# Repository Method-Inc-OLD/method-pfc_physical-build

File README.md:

# Method Personal Food Computer – Physical Build

Documentation of the mechanical and electrical design of [Method](Http://www.method.com)'s Personal Food Computer 

## Overview
The Method PFC is a version of OpenAg's Personal Food Computer. It was built to be more modular and incorporate recycled material. This repository contains:
- [Mechanical](/Mechanical) (Construction and 3D prints)
- [Electrical](/Electrical) (Circuitry)

For Method's custom software, please visit the [method-pfc_device-software](http://www.github.com/method-inc/method-pfc_device-software) repository.

## Credits

Method PFC v1.0 was designed and built by David Mayman, Felix Noller, Adrian Kraus, and Luke Thompson in London.

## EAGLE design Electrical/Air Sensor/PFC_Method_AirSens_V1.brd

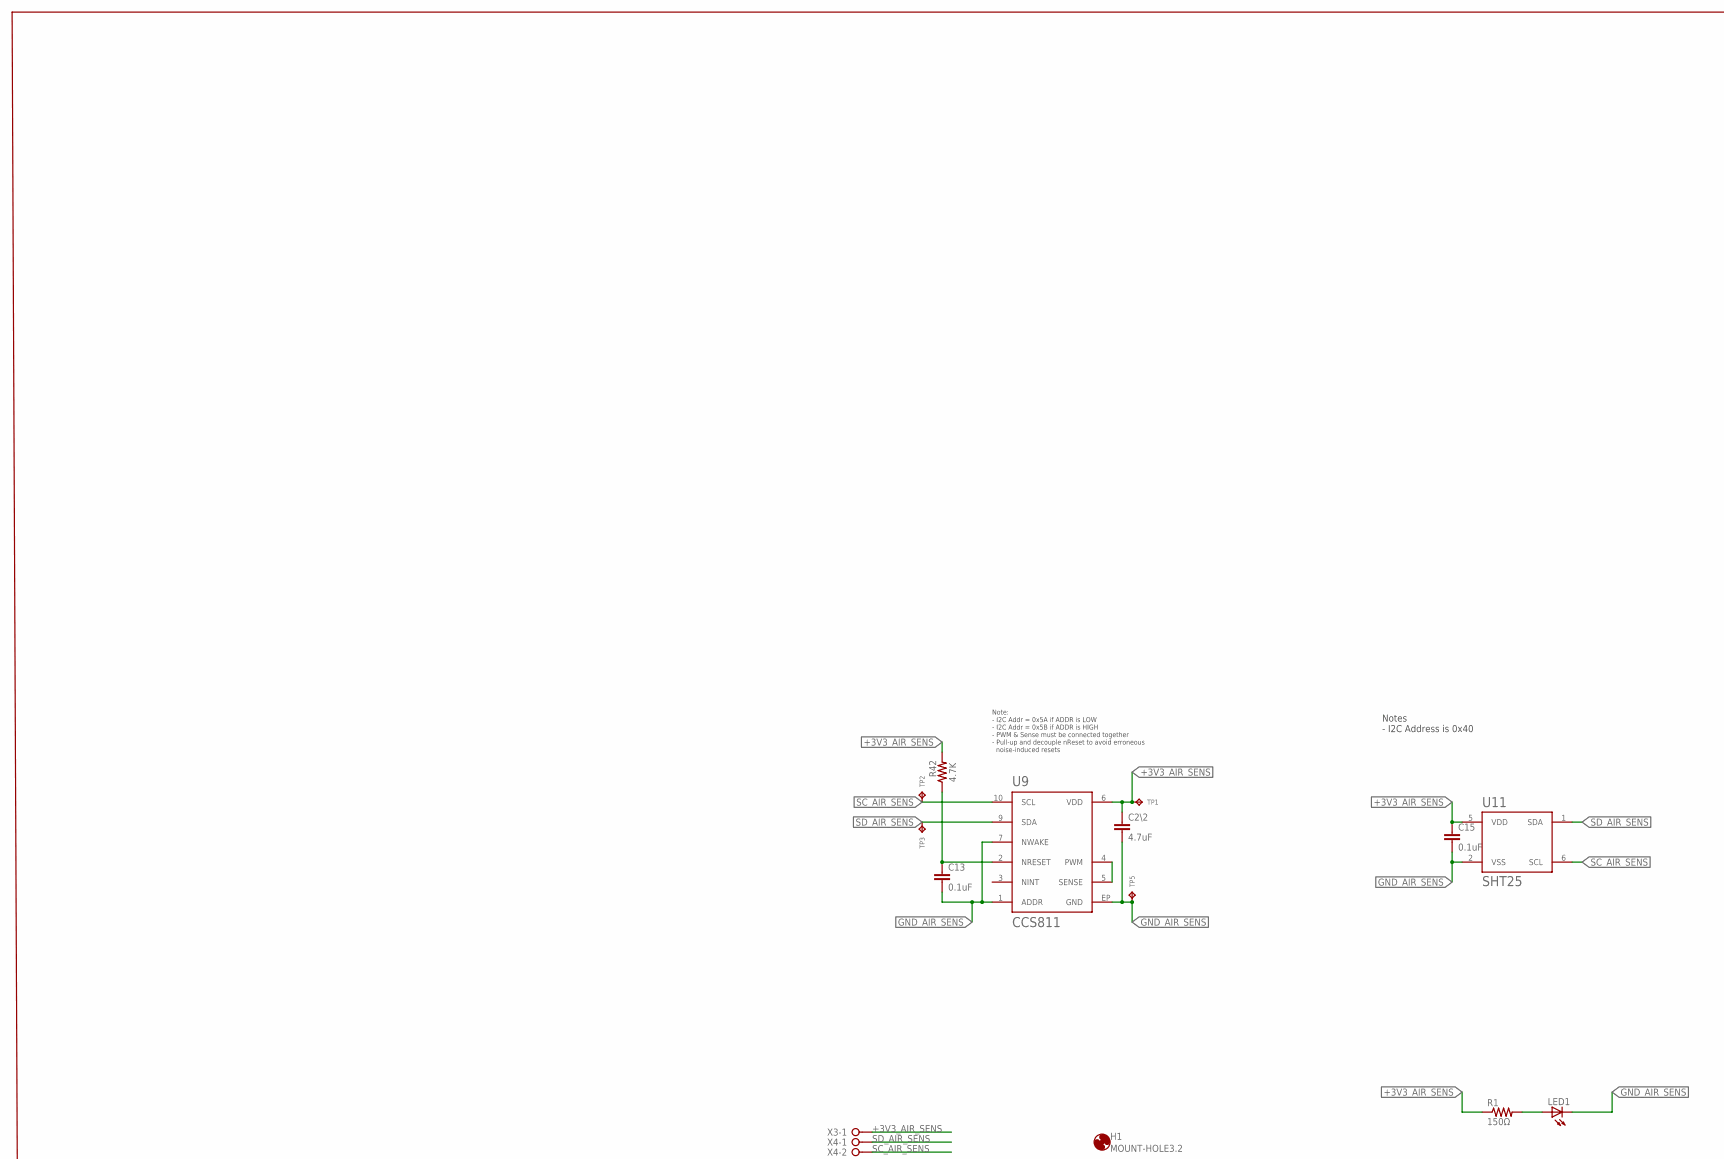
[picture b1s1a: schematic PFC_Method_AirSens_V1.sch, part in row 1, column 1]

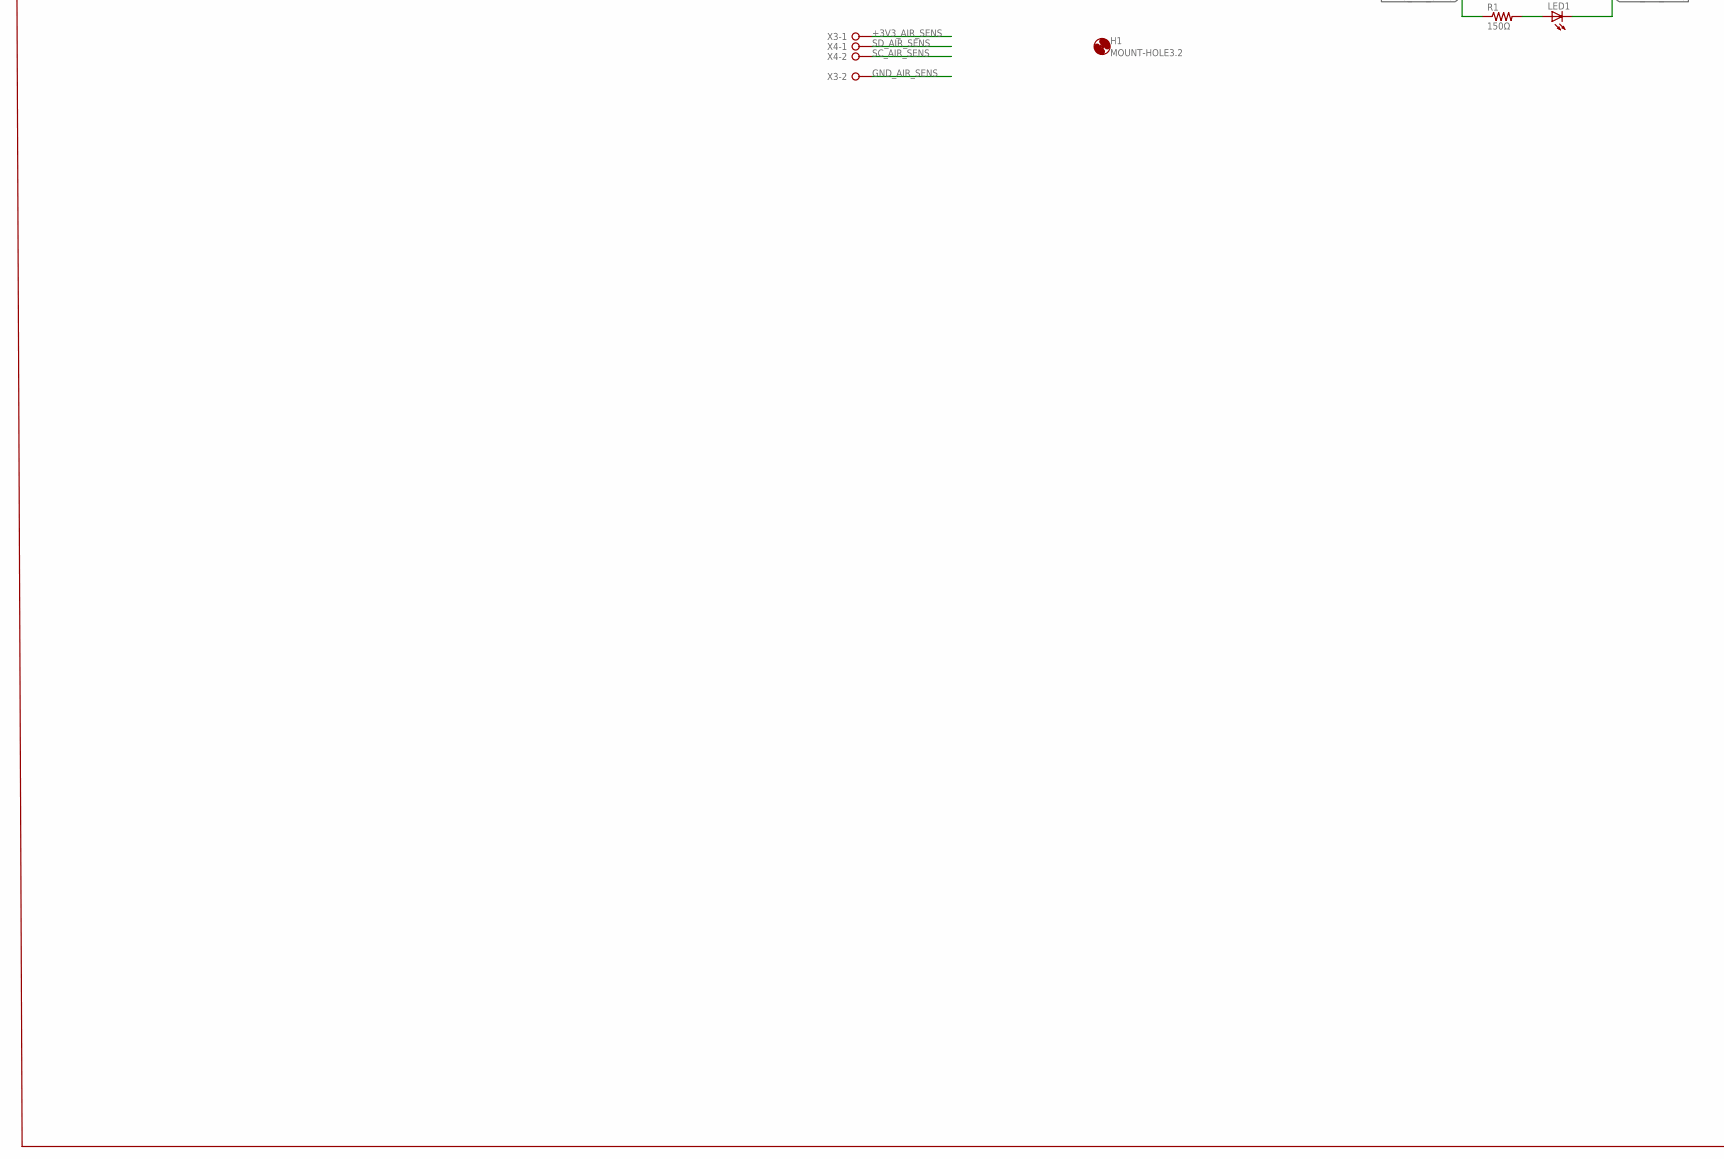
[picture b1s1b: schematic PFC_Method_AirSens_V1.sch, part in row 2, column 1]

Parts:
C2\2: 4.7uF; C0805
C13, C15: 0.1uF; C0603
H1: MOUNT-HOLE3.2; 3,2
LED1: LED5MM
R1: 150Ω; 0207/10
R42: 4.7K; R1206
TP1, TP2, TP3, TP5: TPTP06R; TP06R
U9: CCS811
U11: SHT25; SHT2X
X3, X4: W237-02P; W237-132

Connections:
+3V3_AIR_SENS: C2\2.1, C15.1, R1.1, R42.2, TP1.TP, U9.6 (VDD), U11.5 (VDD), X3.1
GND_AIR_SENS: C2\2.2, C13.2, C15.2, LED1.K (C), TP5.TP, U9.1 (ADDR), U9.7 (NWAKE), U9.EP (GND), U11.2 (VSS), X3.2
unnamed: LED1.A, R1.2
unnamed: U9.4 (PWM), U9.5 (SENSE)
unnamed: C13.1, R42.1, U9.2 (NRESET)
SC_AIR_SENS: TP2.TP, U9.10 (SCL), U11.6 (SCL), X4.2
SD_AIR_SENS: TP3.TP, U9.9 (SDA), U11.1 (SDA), X4.1

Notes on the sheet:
Original Board by Dan Poitrast
Change Log:
Released under the Creative Commons Attribution Share-Alike 4.0 License https://creativecommons.org/licenses/by-sa/4.0/
Note: - I2C Addr = 0x5A if ADDR is LOW - I2C Addr = 0x5B if ADDR is HIGH - PWM & Sense must be connected together - Pull-up and decouple nReset to avoid erroneous noise-induced resets
Notes - I2C Address is 0x40

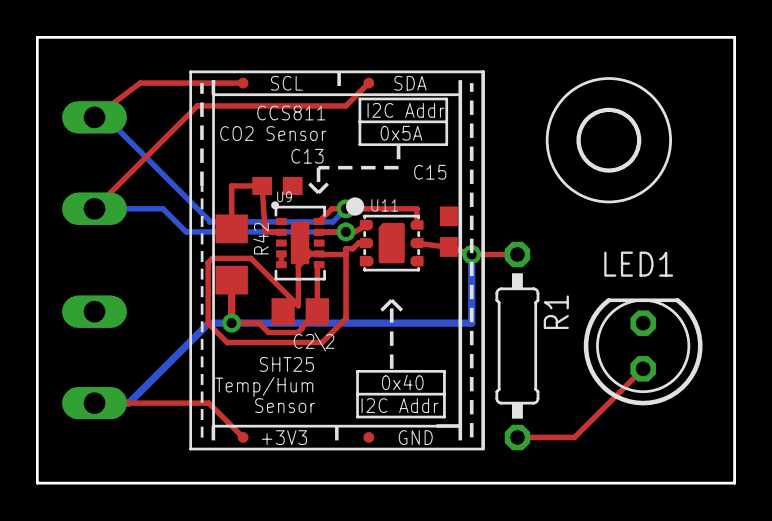
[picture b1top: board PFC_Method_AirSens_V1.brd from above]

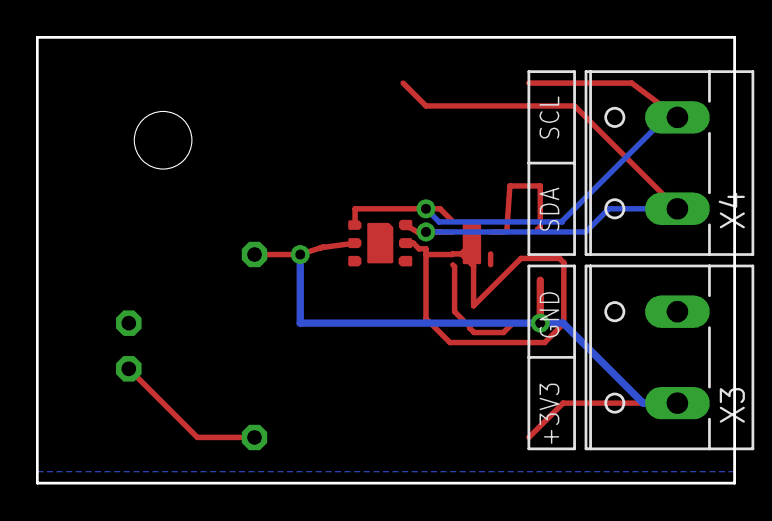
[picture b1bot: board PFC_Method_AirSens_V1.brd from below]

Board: 2 copper layers, 38.7 x 24.8 mm, 15 parts (2 on the bottom side), 7 nets.

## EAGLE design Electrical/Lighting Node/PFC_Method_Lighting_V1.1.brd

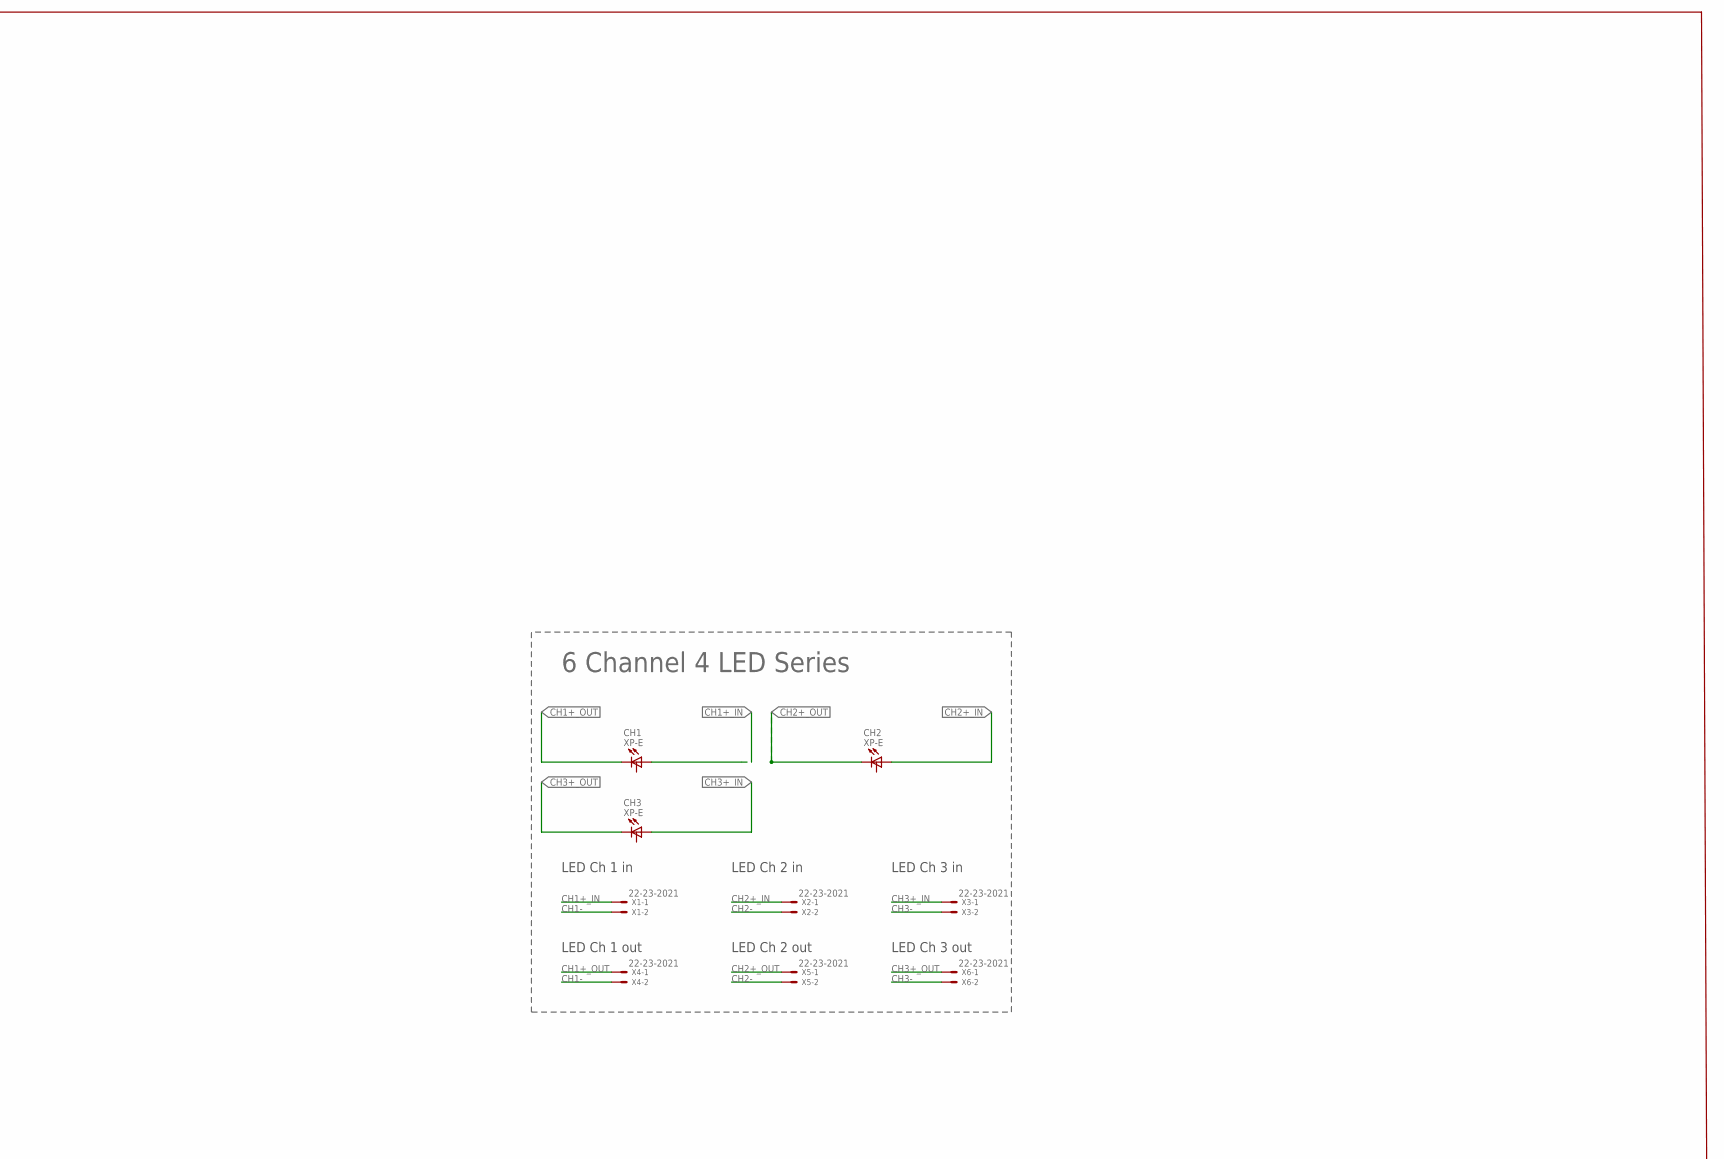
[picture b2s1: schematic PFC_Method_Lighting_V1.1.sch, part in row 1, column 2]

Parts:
CH1, CH2, CH3: XP-E; CREE-XLAMP-XP-E
X1, X2, X3, X4, X5, X6: 22-23-2021

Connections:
CH1+_IN: CH1.A, CH1.A@1 (A), X1.1
CH1+_OUT: CH1.C, CH1.C@1 (C), X4.1
CH1-: X1.2, X4.2
CH2+_IN: CH2.A, CH2.A@1 (A), X2.1
CH2+_OUT: CH2.C, CH2.C@1 (C), X5.1
CH2-: X2.2, X5.2
CH3+_IN: CH3.A, CH3.A@1 (A), X3.1
CH3+_OUT: CH3.C, CH3.C@1 (C), X6.1
CH3-: X3.2, X6.2

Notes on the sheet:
Original Board by Dan Poitrast
Change Log:
Released under the Creative Commons Attribution Share-Alike 4.0 License https://creativecommons.org/licenses/by-sa/4.0/
6 Channel 4 LED Series
LED Ch 1 out
LED Ch 2 out
LED Ch 3 out
LED Ch 1 in
LED Ch 2 in
LED Ch 3 in

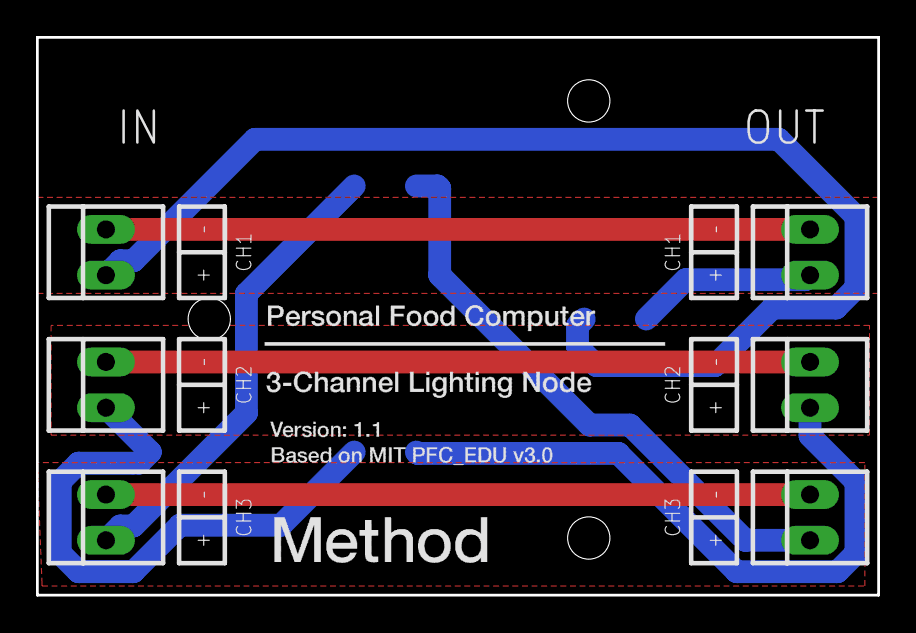
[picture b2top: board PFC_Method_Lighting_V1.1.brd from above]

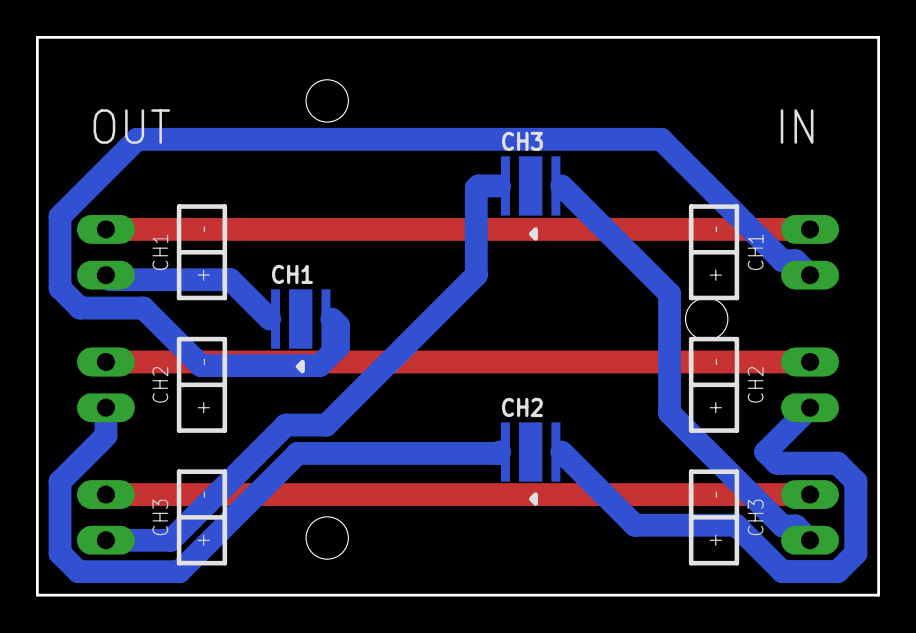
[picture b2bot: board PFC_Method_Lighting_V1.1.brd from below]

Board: 2 copper layers, 46.7 x 31.0 mm, 9 parts (3 on the bottom side), 9 nets.

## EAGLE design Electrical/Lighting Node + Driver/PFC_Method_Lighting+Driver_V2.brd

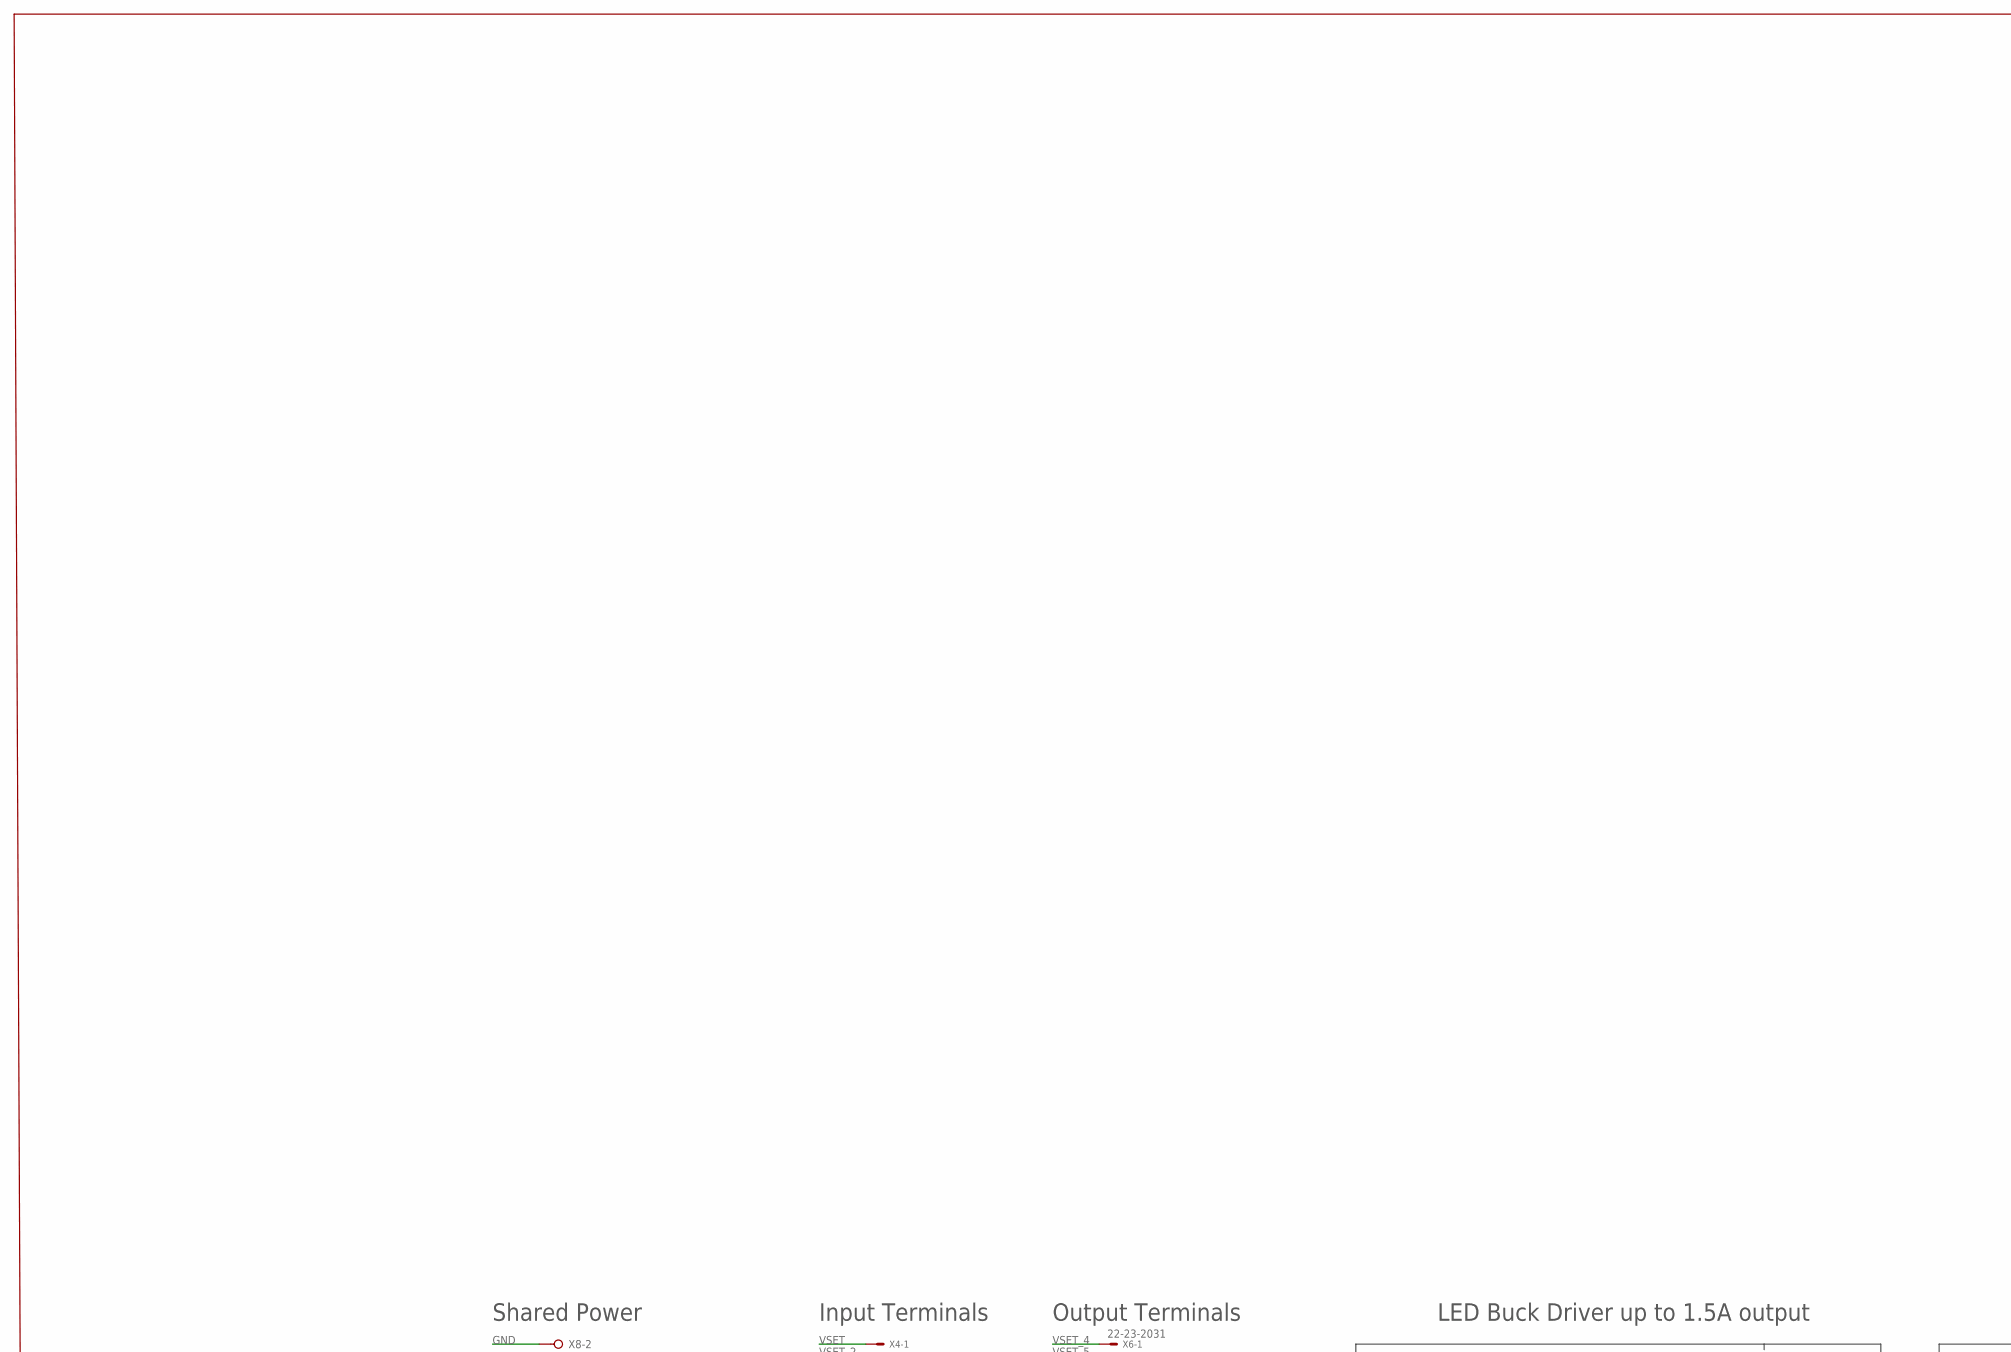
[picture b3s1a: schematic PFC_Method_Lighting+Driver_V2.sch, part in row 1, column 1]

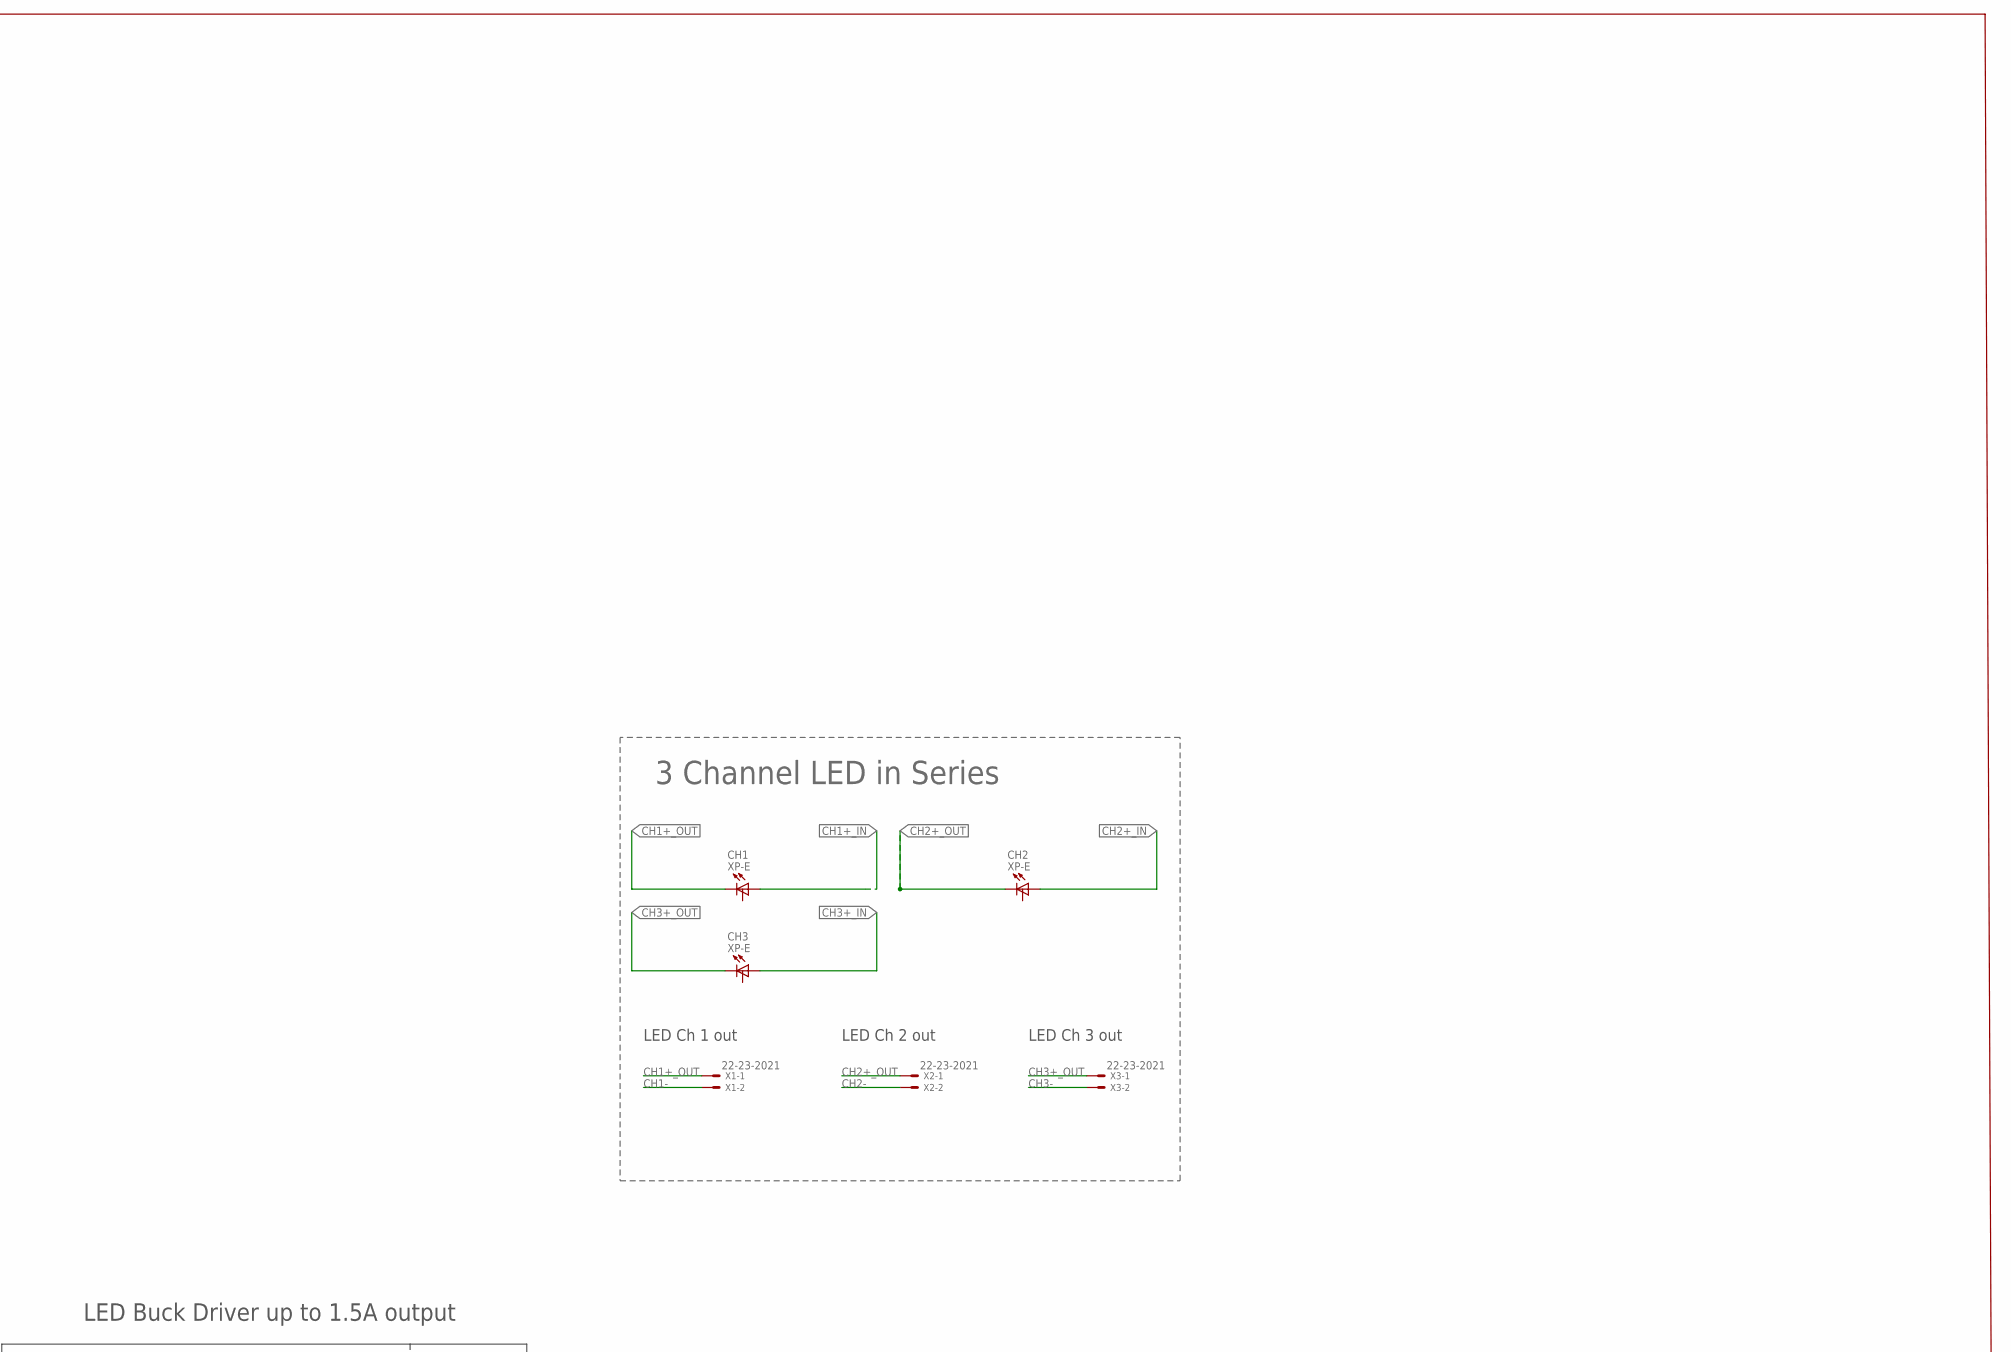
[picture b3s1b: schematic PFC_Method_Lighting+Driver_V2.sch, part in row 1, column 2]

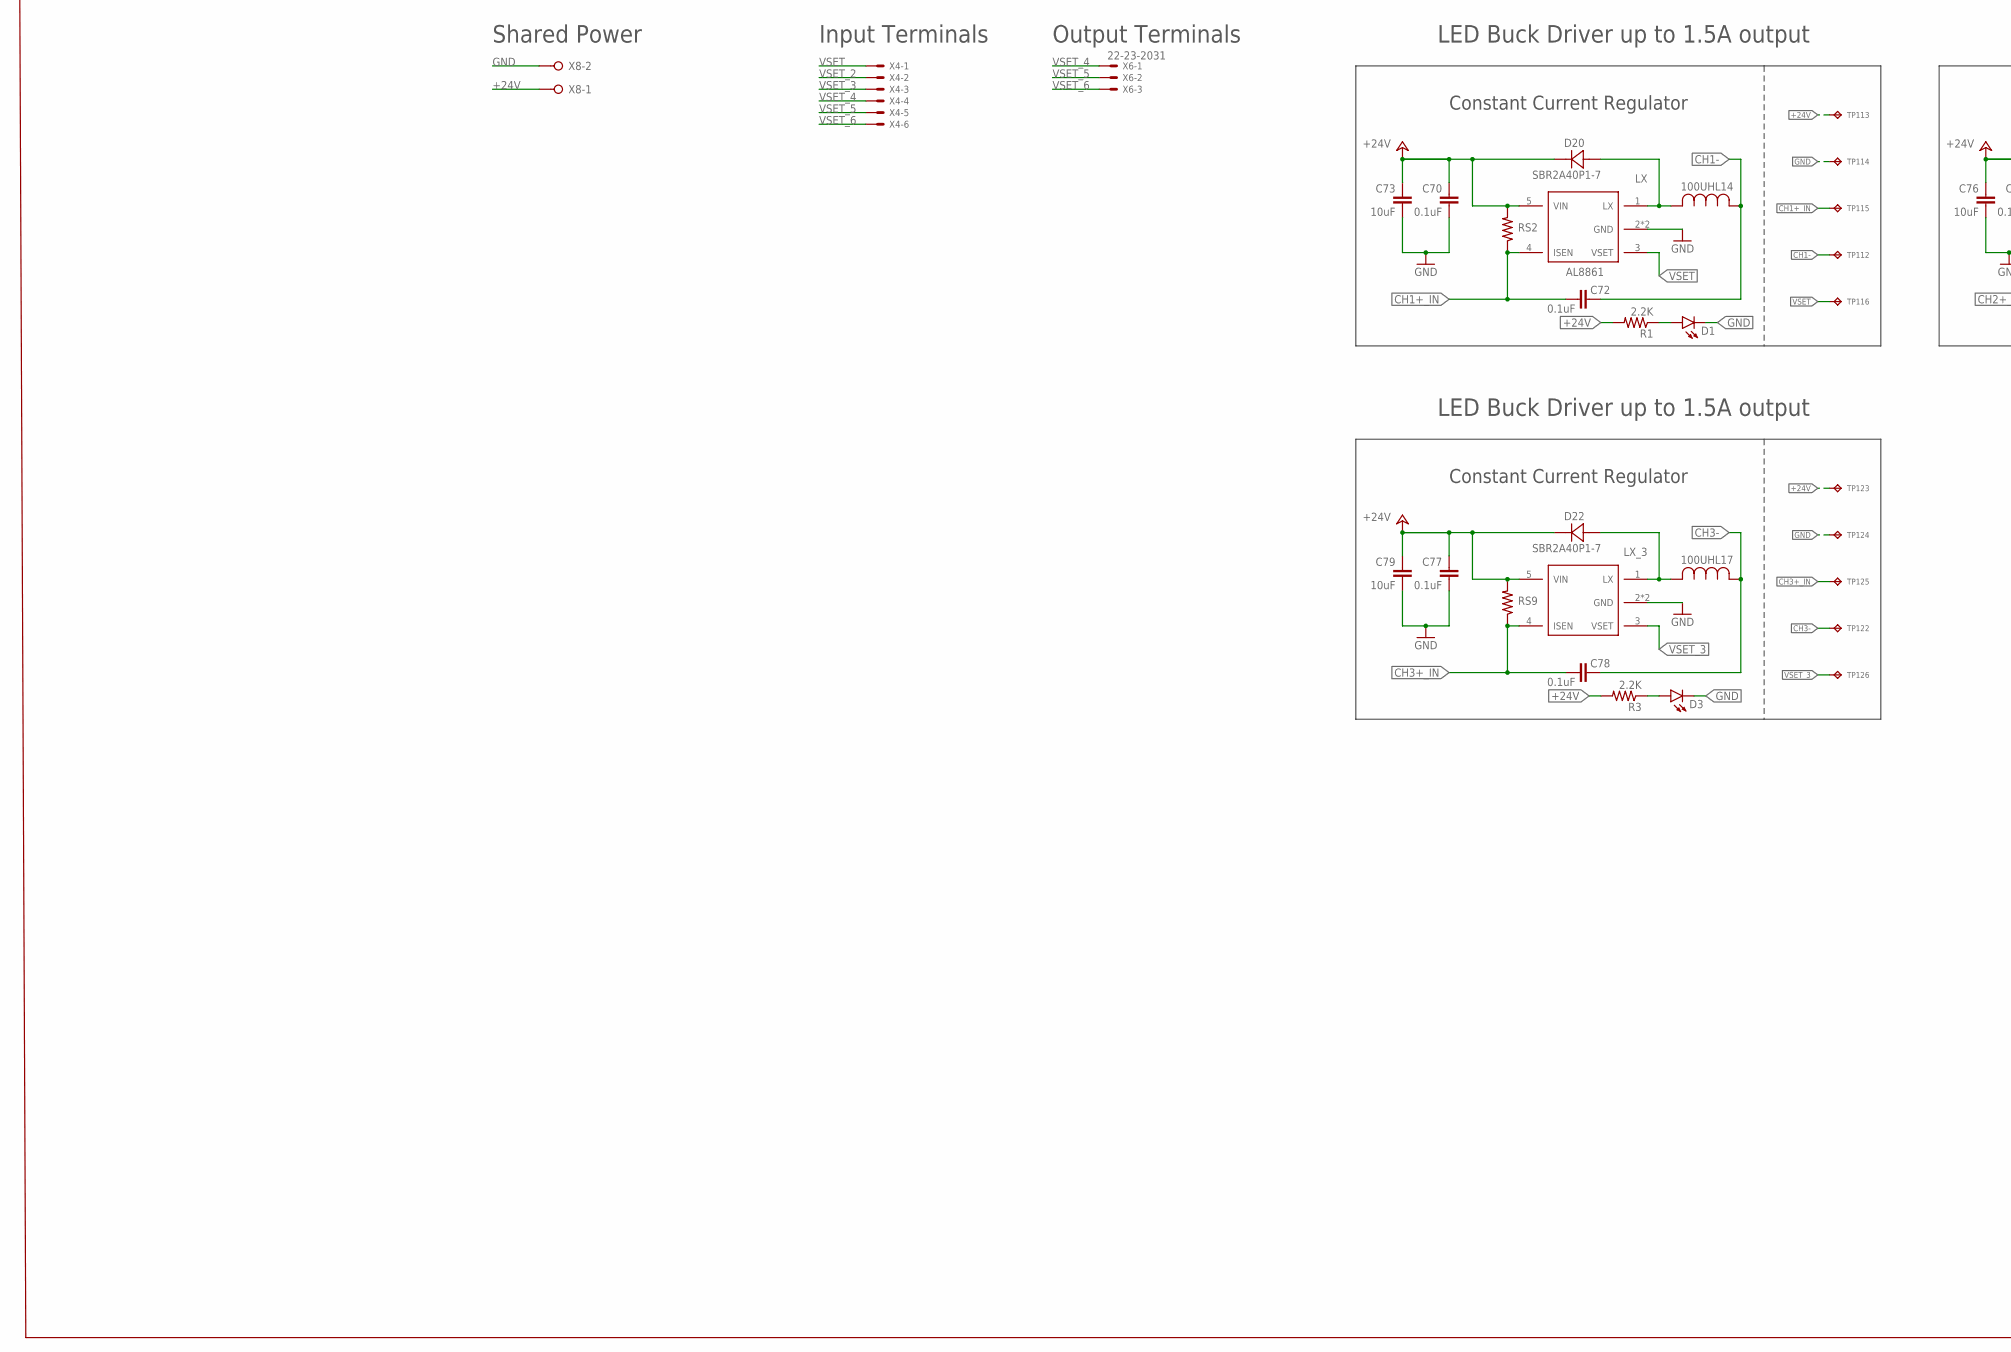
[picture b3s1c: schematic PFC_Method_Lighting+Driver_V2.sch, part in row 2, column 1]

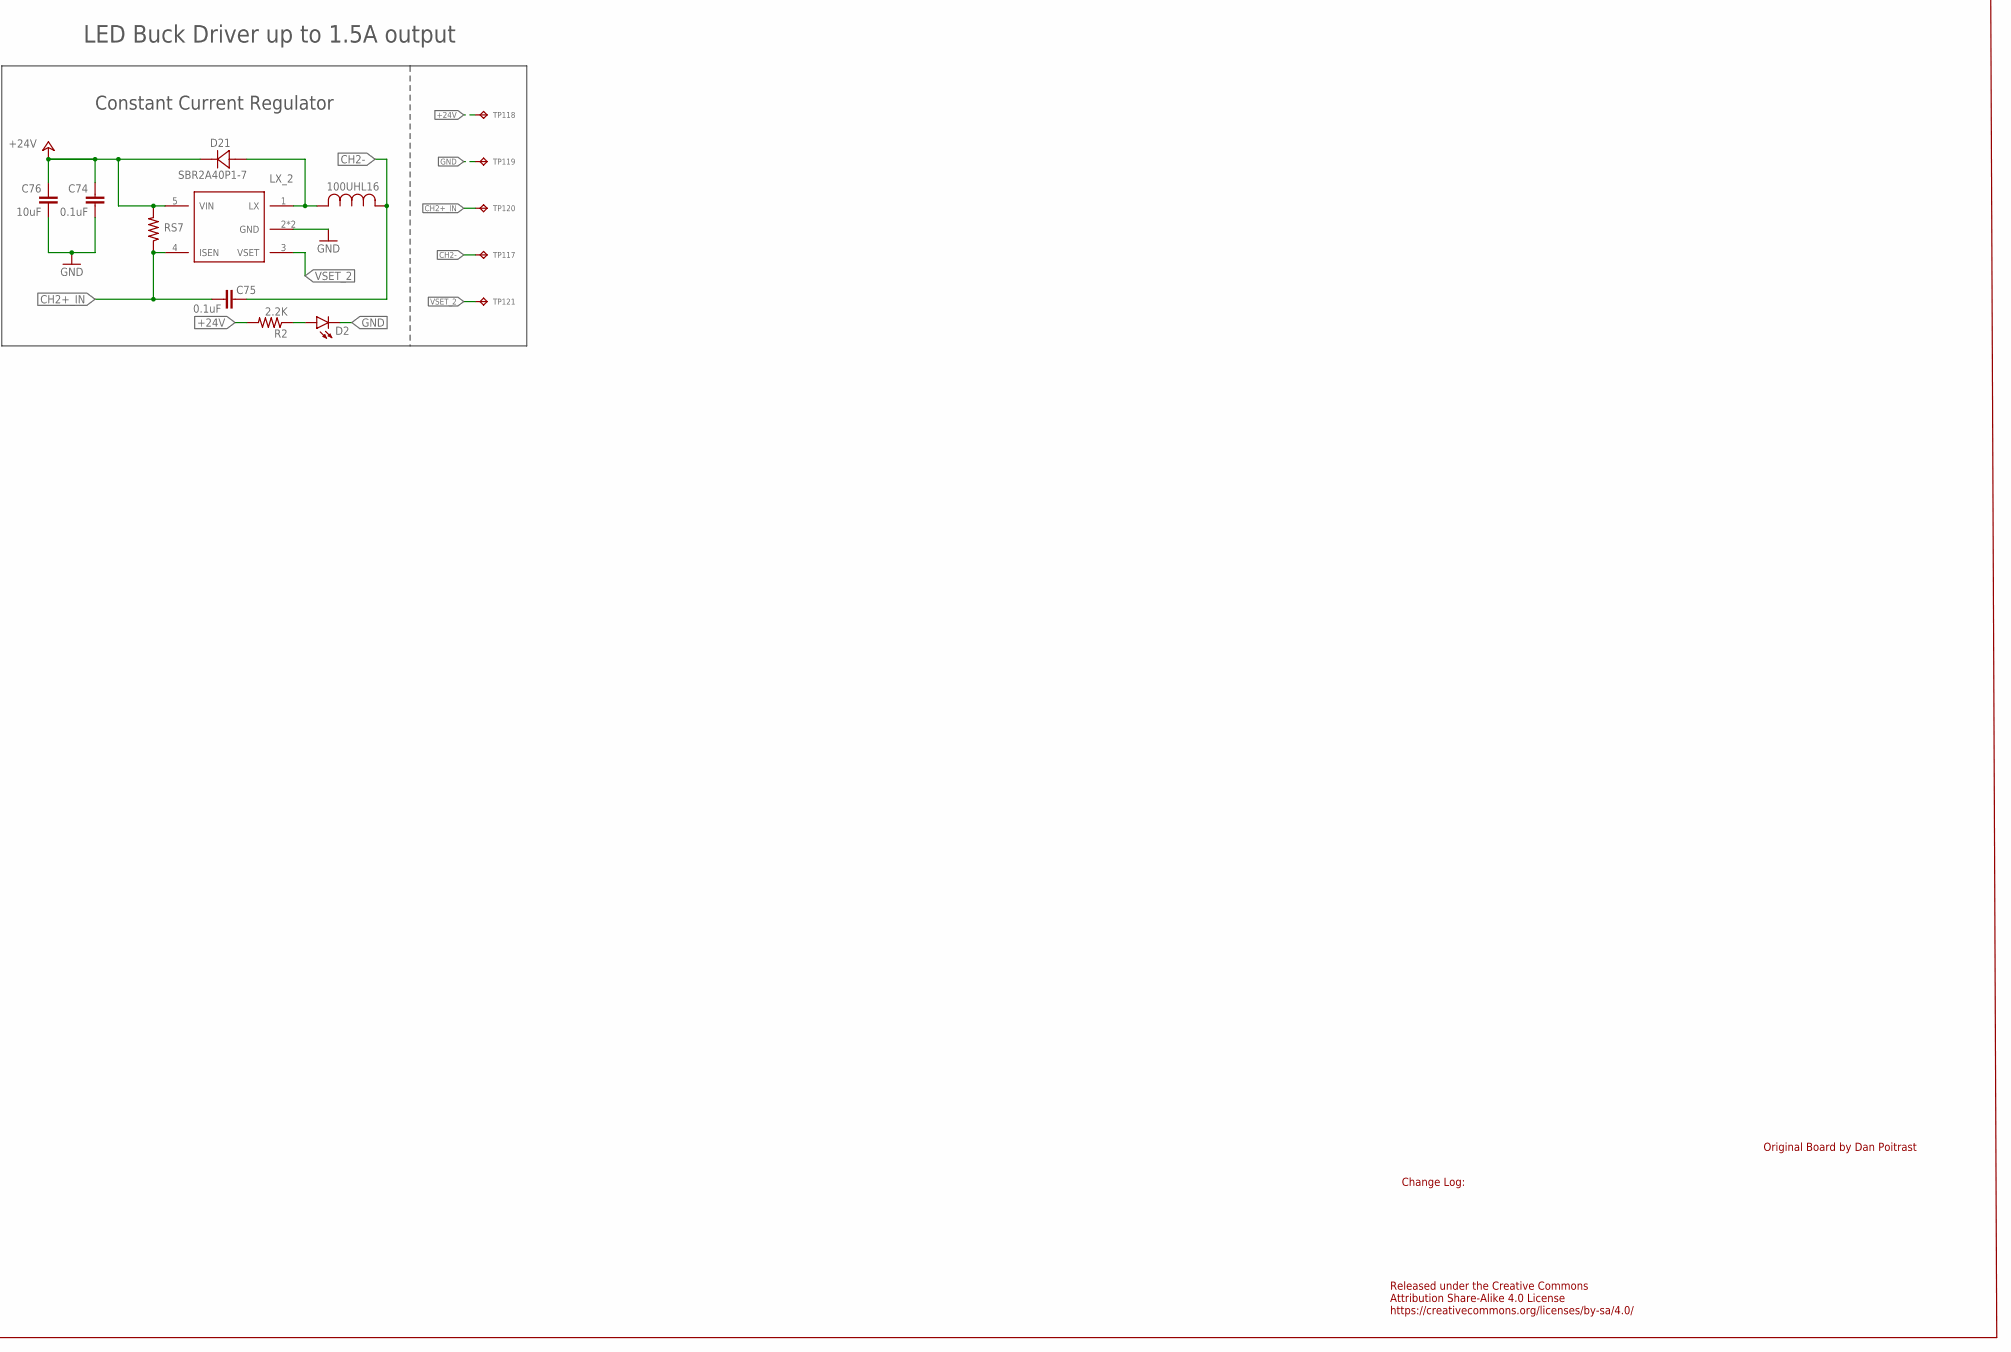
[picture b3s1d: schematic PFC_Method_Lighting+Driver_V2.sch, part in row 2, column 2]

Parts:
C70, C72, C74, C75, C77, C78: 0.1uF; C0603
C73, C76, C79: 10uF; C0805
CH1, CH2, CH3: XP-E; CREE-XLAMP-XP-E
D1, D2, D3: LED5MM; LED_5MM
D20, D21, D22: SBR2A40P1-7; POWERDI123
L14, L16, L17: 100UH; IND_BOURNS_SDR1307
R1, R2, R3: 2.2K; 0207/10
RS2: 6.34Ω; R0805
RS7, RS9: 6.34 Ω; R0805
TP112, TP113, TP114, TP115, TP116, TP117, TP118, TP119, TP120, TP121, TP122, TP123, TP124, TP125, TP126: TPTP06R; TP06R
U$25, U$26, U$27: AL8861
X1, X2, X3: 22-23-2021
X4: 22-23-2061
X6: 22-23-2031
X8: W237-02P; W237-132

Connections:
+24V: C70.1, C73.1, C74.1, C76.1, C77.1, C79.1, D20.-, D21.-, D22.-, R1.2, R2.2, R3.2, RS2.2, RS7.2, RS9.2, TP113.TP, TP118.TP, TP123.TP, U$25.5 (VIN), U$26.5 (VIN), U$27.5 (VIN), X8.1
CH1+_IN: C72.2, CH1.A, CH1.A@1 (A), RS2.1, TP115.TP, U$25.4 (ISEN)
CH1+_OUT: CH1.C, CH1.C@1 (C), X1.1
CH1-: C72.1, L14.2, TP112.TP, X1.2
CH2+_IN: C75.2, CH2.A, CH2.A@1 (A), RS7.1, TP120.TP, U$26.4 (ISEN)
CH2+_OUT: CH2.C, CH2.C@1 (C), X2.1
CH2-: C75.1, L16.2, TP117.TP, X2.2
CH3+_IN: C78.2, CH3.A, CH3.A@1 (A), RS9.1, TP125.TP, U$27.4 (ISEN)
CH3+_OUT: CH3.C, CH3.C@1 (C), X3.1
CH3-: C78.1, L17.2, TP122.TP, X3.2
GND: C70.2, C73.2, C74.2, C76.2, C77.2, C79.2, D1.K (C), D2.K (C), D3.K (C), TP114.TP, TP119.TP, TP124.TP, U$25.2 (GND), U$25.44 (GND), U$26.2 (GND), U$26.44 (GND), U$27.2 (GND), U$27.44 (GND), X8.2
LX: D20.+, L14.1, U$25.1 (LX)
LX_2: D21.+, L16.1, U$26.1 (LX)
LX_3: D22.+, L17.1, U$27.1 (LX)
unnamed: D2.A, R2.1
unnamed: D1.A, R1.1
unnamed: D3.A, R3.1
VSET: TP116.TP, U$25.3 (VSET), X4.1
VSET_2: TP121.TP, U$26.3 (VSET), X4.2
VSET_3: TP126.TP, U$27.3 (VSET), X4.3
VSET_4: X4.4, X6.1
VSET_5: X4.5, X6.2
VSET_6: X4.6, X6.3

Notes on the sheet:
Original Board by Dan Poitrast
Change Log:
Released under the Creative Commons Attribution Share-Alike 4.0 License https://creativecommons.org/licenses/by-sa/4.0/
3 Channel LED in Series
LED Buck Driver up to 1.5A output
Constant Current Regulator
LED Ch 1 out
LED Ch 2 out
LED Ch 3 out
Input Terminals
Output Terminals
Shared Power
AL8861

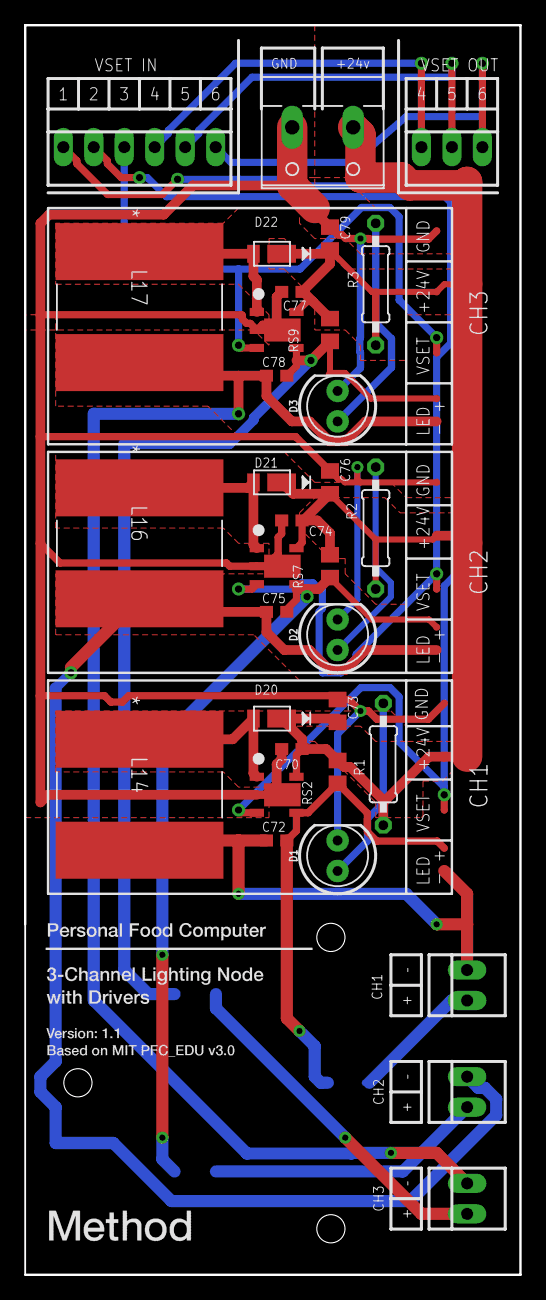
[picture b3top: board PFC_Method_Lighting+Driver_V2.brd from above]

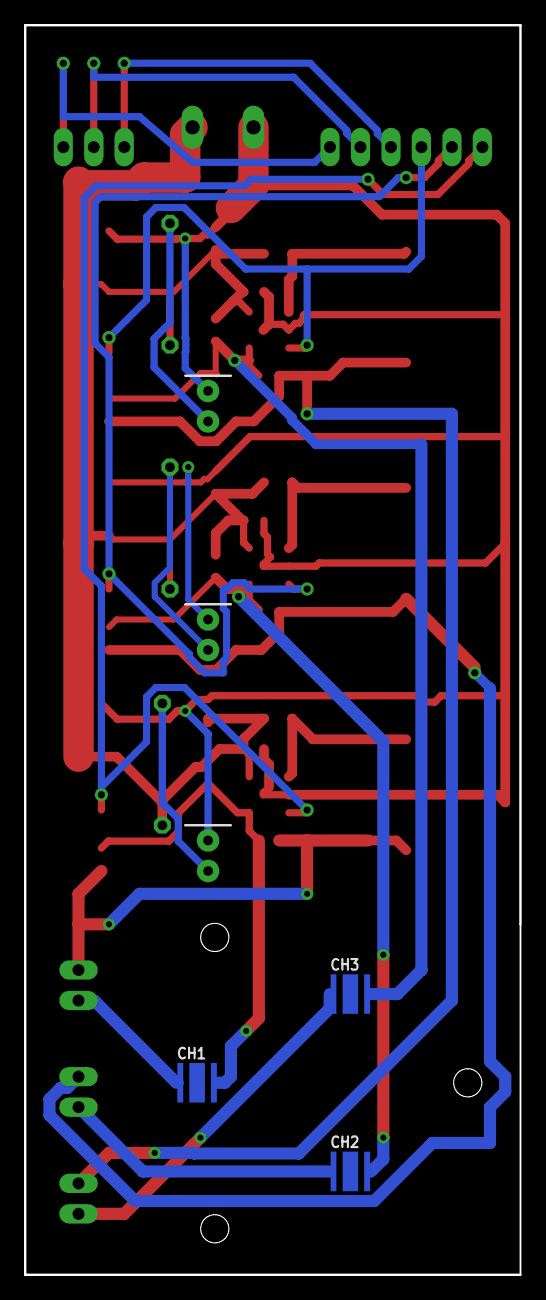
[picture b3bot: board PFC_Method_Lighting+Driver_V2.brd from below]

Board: 2 copper layers, 41.3 x 104.1 mm, 51 parts (3 on the bottom side), 23 nets.

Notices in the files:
parts and their libraries:
SparkFun-LED: Licensing: Creative Commons ShareAlike 4.0 International - https://creativecommons.org/licenses/by-sa/4.0
